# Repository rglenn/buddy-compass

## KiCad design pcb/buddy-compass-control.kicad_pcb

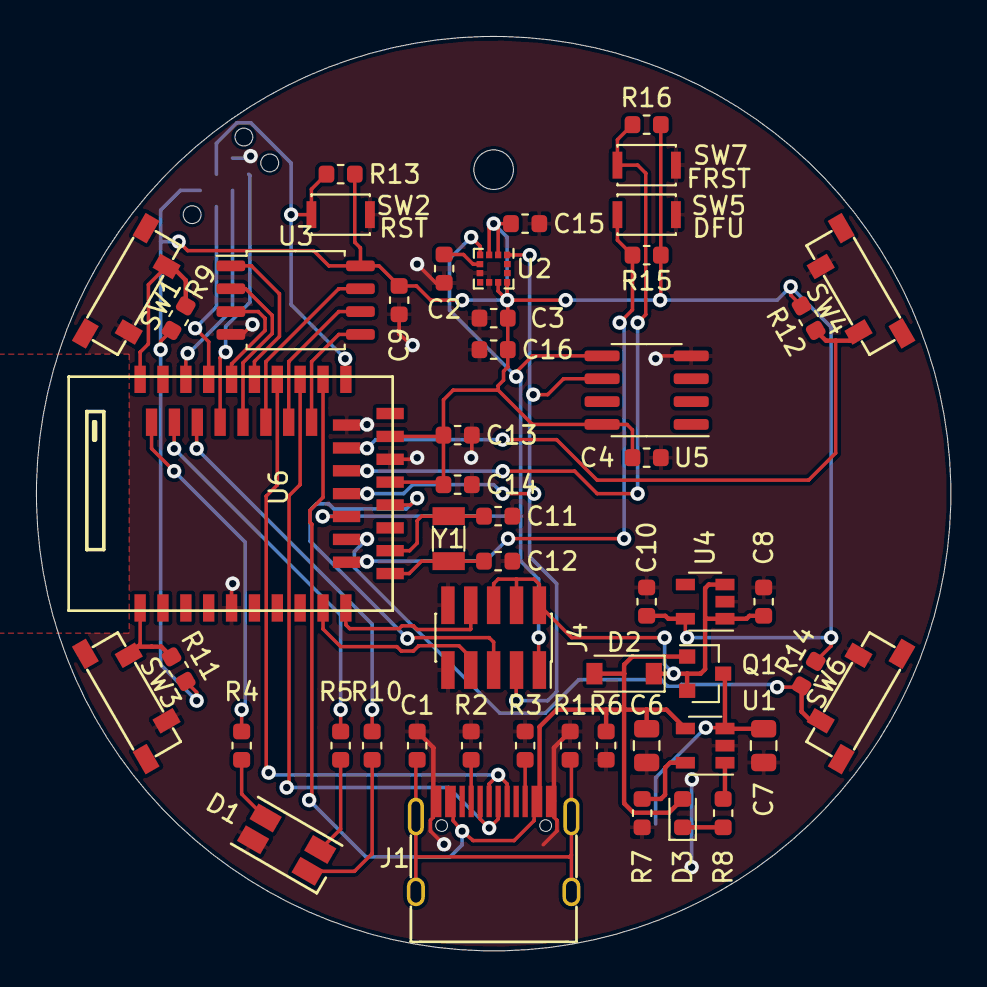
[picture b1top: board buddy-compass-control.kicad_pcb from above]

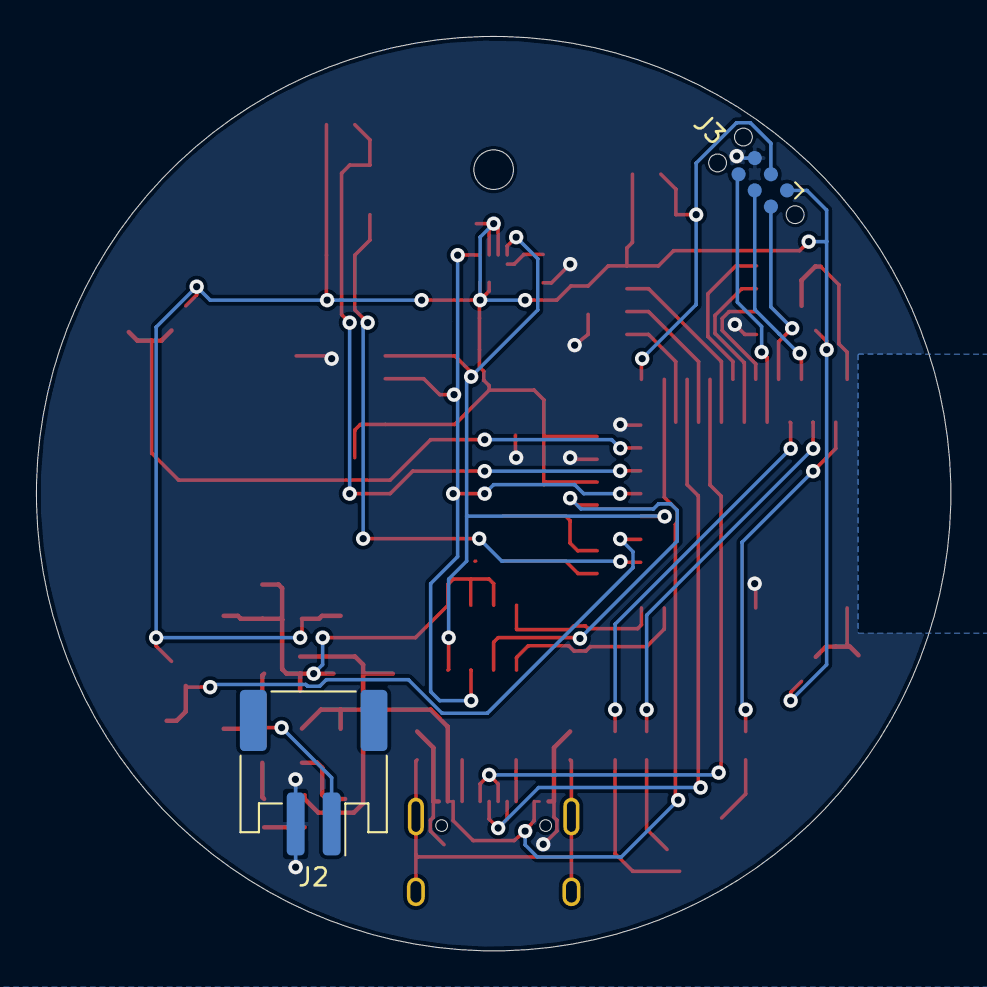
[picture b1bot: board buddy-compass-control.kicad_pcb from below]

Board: 2 copper layers, 50.8 x 50.8 mm, 54 parts (2 on the bottom side), 43 nets.

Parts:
C1, C3, C4, C9, C14, C15: 100n; C_0603_1608Metric
C2: 220n; C_0603_1608Metric
C6, C7: 4.7u; C_0805_2012Metric
C8, C10, C13, C16: 1u; C_0603_1608Metric
C11, C12: 12p; C_0603_1608Metric
D1: LED_RGBC; LED_RGB_1210
D2: MBR0520; D_SOD-123
D3: LED; LED_0603_1608Metric
H1: MountingHole; MountingHole_2.2mm_M2_DIN965
J1: USB_C_Receptacle_USB2.0; USB_C_Receptacle_GT-USB-7010
J2: Conn_01x02; JST_PH_S2B-PH-SM4-TB_1x02-1MP_P2.00mm_Horizontal
J3: Conn_02x03_Odd_Even; Tag-Connect_TC2030-IDC-NL_2x03_P1.27mm_Vertical
J4: Conn_02x05_Odd_Even; PinSocket_2x05_P1.27mm_Vertical_SMD
Q1: DMG2301L; SOT-23
R1: 1M; R_0603_1608Metric
R2, R3: 5.1K; R_0603_1608Metric
R4, R5, R10: 220; R_0603_1608Metric
R6: 100K; R_0603_1608Metric
R7: 2K; R_0603_1608Metric
R8: 1K; R_0603_1608Metric
R9, R11, R12, R13, R14, R15, R16: 47K; R_0603_1608Metric
SW1, SW3, SW4, SW6: SW_Push; TS-1236VW
SW2, SW5, SW7: SW_Push; SW_SPST_CK_KXT3
U1: MCP73831-2-OT; SOT-23-5
U2: LSM303C; LGA-12_2x2mm_Pitch0.5mm
U3: W25Q32JVSS; SOIC-8_5.23x5.23mm_P1.27mm
U4: MIC5504-3.3YM5; SOT-23-5
U5: ATECC608A-SSHDA; SOIC-8_3.9x4.9mm_P1.27mm
U6: E73-2G4M08S1C
Y1: 32.768KHz; Crystal_SMD_3215-2Pin_3.2x1.5mm

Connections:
+3V3: C3.1, C4.1, C9.1, C10.1, C13.1, C14.1, C15.1, C16.1, J3.1, R9.1, R11.1, R12.1, R13.1, R14.1, R15.1, R16.1, U2.2, U2.3, U2.9, U2.10, U3.8, U4.5, U5.8, U6.19, U6.23
/BUTTON1: R9.2, SW1.1, U6.43
/BUTTON3: R11.2, SW3.1, U6.1
/BUTTON4: R12.2, SW4.1, U6.22
/BUTTON6: R14.2, SW6.1, U6.14
/D+: J1.A6, J1.B6, U6.31
/D-: J1.A7, J1.B7, U6.29
/DFU: R15.2, SW5.1, U6.12
/DISPLAY_IO1: J4.7, U6.9
/DISPLAY_IO2: J4.8, U6.10
/FRST: R16.2, SW7.1, U6.20
/QSPI_CS: U3.1, U6.33
/QSPI_D0: U3.5, U6.28
/QSPI_D1: U3.2, U6.34
/QSPI_D2: U3.3, U6.35
/QSPI_D3: U3.7, U6.32
/QSPI_SCK: U3.6, U6.30
/RESET: J3.3, R13.2, SW2.1, U6.26
/SCL: J4.3, U2.1, U5.6, U6.18
/SDA: J4.1, U2.4, U5.5, U6.16
/SDB: J4.5, U6.17
/STATUS_B: R4.1, U6.42
/STATUS_G: R5.1, U6.40
/STATUS_R: R10.1, U6.38
/SWC: J3.4, U6.39
/SWD: J3.2, U6.37
/SWO: J3.6, U6.36
GND: C1.2, C2.2, C3.2, C4.2, C6.2, C7.2, C8.2, C9.2, C10.2, C11.2, C12.2, C13.2, C14.2, C15.2, C16.2, D1.4, J1.A1, J1.A12, J1.B1, J1.B12, J2.2, J3.5, J4.9, J4.10, R1.2, R2.2, R3.2, R6.2, R7.2, SW1.2, SW2.2, SW3.2, SW4.2, SW5.2, SW6.2, SW7.2, U1.2, U2.6, U2.8, U3.4, U4.2, U5.4, U6.5, U6.21, U6.24
unnamed: C1.1, J1.S1, R1.1
unnamed: C2.1, U2.5
unnamed: C7.1, J2.1, Q1.3, U1.3
unnamed: C11.1, U6.13, Y1.2
unnamed: C12.1, U6.11, Y1.1
unnamed: D1.1, R10.2
unnamed: D1.2, R5.2
unnamed: D1.3, R4.2
unnamed: D3.1, R8.1
unnamed: J1.A5, R2.1
unnamed: J1.B5, R3.1
unnamed: R7.1, U1.5
unnamed: R8.2, U1.1
VBUS: C6.1, D2.2, D3.2, J1.A4, J1.A9, J1.B4, J1.B9, Q1.1, R6.1, U1.4, U6.27
VCC: C8.1, D2.1, J4.2, J4.4, J4.6, Q1.2, U4.1, U4.3

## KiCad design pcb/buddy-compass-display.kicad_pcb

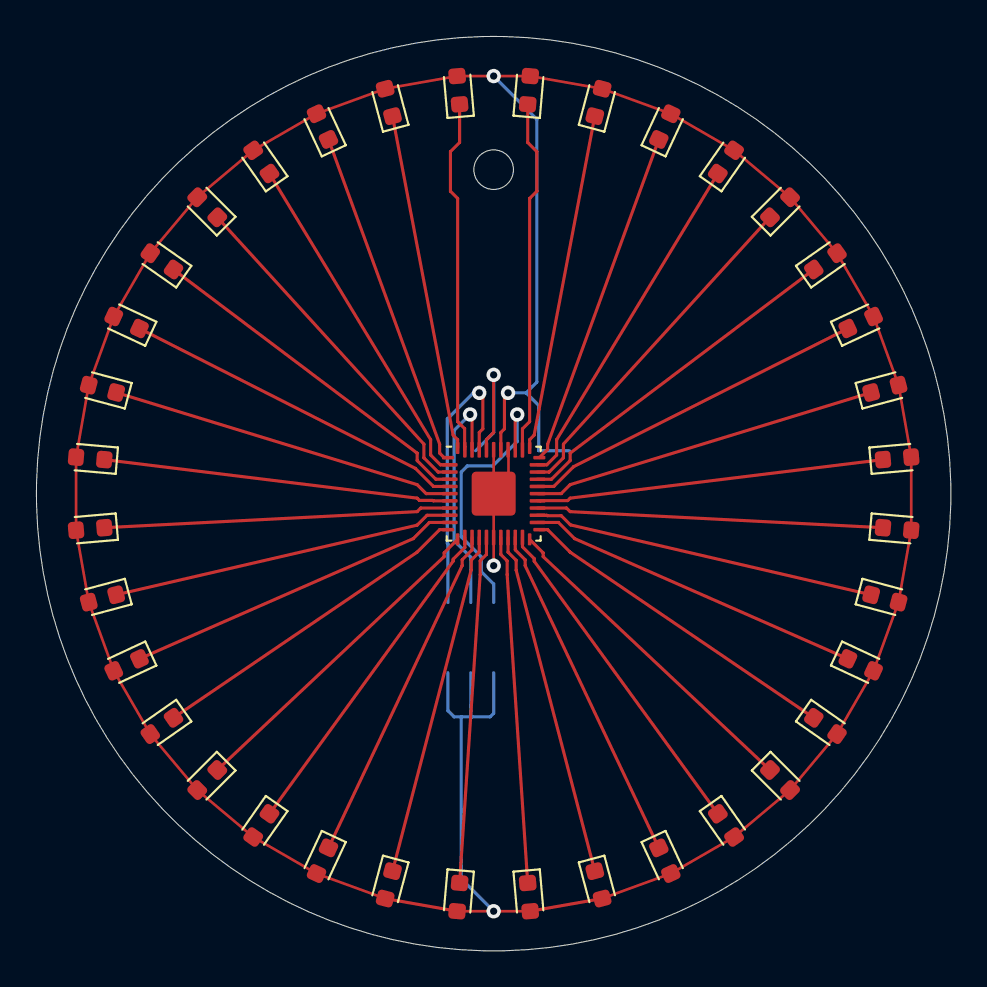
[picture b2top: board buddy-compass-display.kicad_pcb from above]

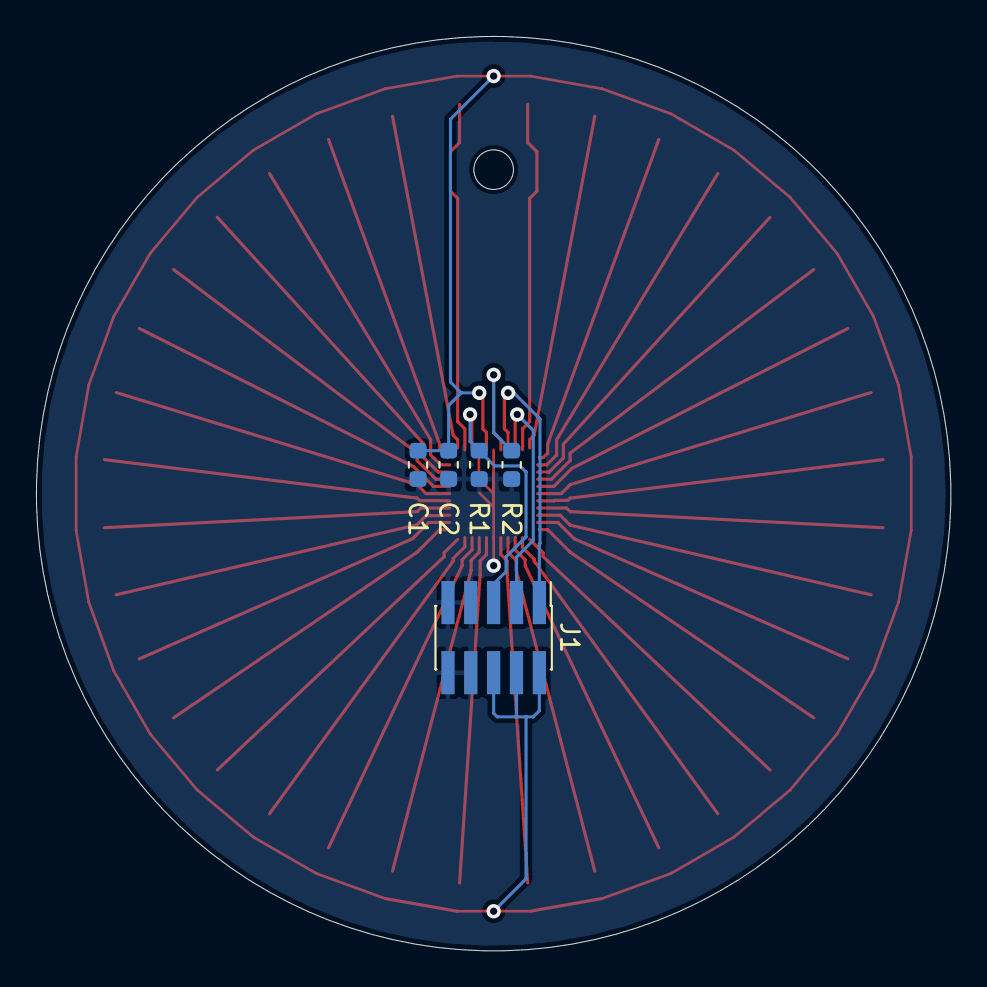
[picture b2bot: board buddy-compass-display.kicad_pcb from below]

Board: 2 copper layers, 50.8 x 50.8 mm, 43 parts (5 on the bottom side), 42 nets.

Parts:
C1: 1u; C_0603_1608Metric
C2: 100n; C_0603_1608Metric
D1, D2, D3, D4, D5, D6, D7, D8, D9, D10, D11, D12, D13, D14, D15, D16, D17, D18, D19, D20, D21, D22, D23, D24, D25, D26, D27, D28, D29, D30, D31, D32, D33, D34, D35, D36: LED; LED_0603_1608Metric
H1: MountingHole; MountingHole_2.2mm_M2_DIN965
J1: Conn_02x05_Odd_Even; PinHeader_2x05_P1.27mm_Vertical_SMD
R1: 100K; R_0603_1608Metric
R2: 3.3K; R_0603_1608Metric
U1: IS31FL3236A; QFN-44-1EP_5x5mm_P0.4mm_EP2.45x2.45mm

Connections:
/SCL: J1.3, U1.42
/SDA: J1.1, U1.41
/SDB: J1.5, R1.1, U1.36
GND: C1.2, C2.2, J1.7, J1.8, J1.9, J1.10, R1.2, R2.2, U1.17, U1.37, U1.39, U1.45
unnamed: D1.1, U1.35
unnamed: D2.1, U1.34
unnamed: D3.1, U1.33
unnamed: D4.1, U1.32
unnamed: D5.1, U1.31
unnamed: D6.1, U1.30
unnamed: D7.1, U1.29
unnamed: D8.1, U1.28
unnamed: D9.1, U1.27
unnamed: D10.1, U1.26
unnamed: D11.1, U1.25
unnamed: D12.1, U1.24
unnamed: D13.1, U1.23
unnamed: D14.1, U1.22
unnamed: D15.1, U1.21
unnamed: D16.1, U1.20
unnamed: D17.1, U1.19
unnamed: D18.1, U1.18
unnamed: D19.1, U1.16
unnamed: D20.1, U1.15
unnamed: D21.1, U1.14
unnamed: D22.1, U1.13
unnamed: D23.1, U1.12
unnamed: D24.1, U1.11
unnamed: D25.1, U1.10
unnamed: D26.1, U1.9
unnamed: D27.1, U1.8
unnamed: D28.1, U1.7
unnamed: D29.1, U1.6
unnamed: D30.1, U1.5
unnamed: D31.1, U1.4
unnamed: D32.1, U1.3
unnamed: D33.1, U1.2
unnamed: D34.1, U1.1
unnamed: D35.1, U1.44
unnamed: D36.1, U1.43
unnamed: R2.1, U1.40
VCC: C1.1, C2.1, D1.2, D2.2, D3.2, D4.2, D5.2, D6.2, D7.2, D8.2, D9.2, D10.2, D11.2, D12.2, D13.2, D14.2, D15.2, D16.2, D17.2, D18.2, D19.2, D20.2, D21.2, D22.2, D23.2, D24.2, D25.2, D26.2, D27.2, D28.2, D29.2, D30.2, D31.2, D32.2, D33.2, D34.2, D35.2, D36.2, J1.2, J1.4, J1.6, U1.38

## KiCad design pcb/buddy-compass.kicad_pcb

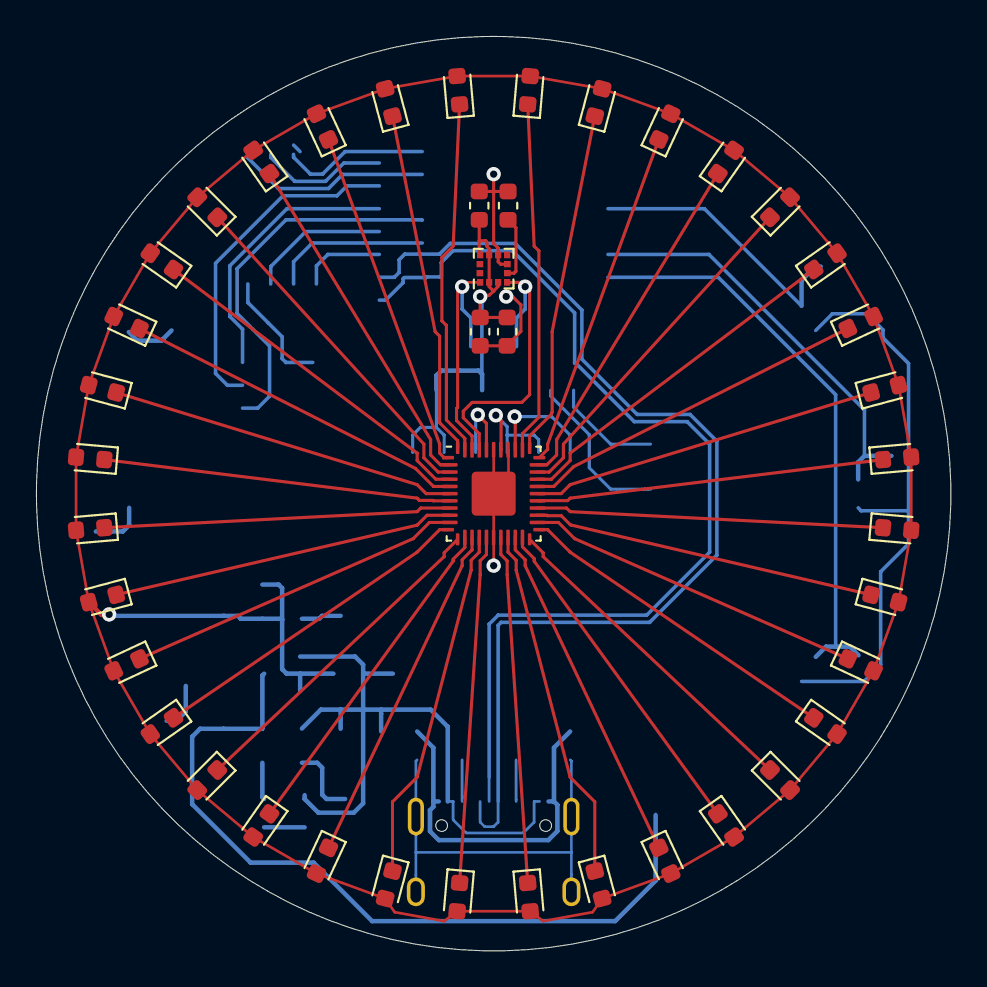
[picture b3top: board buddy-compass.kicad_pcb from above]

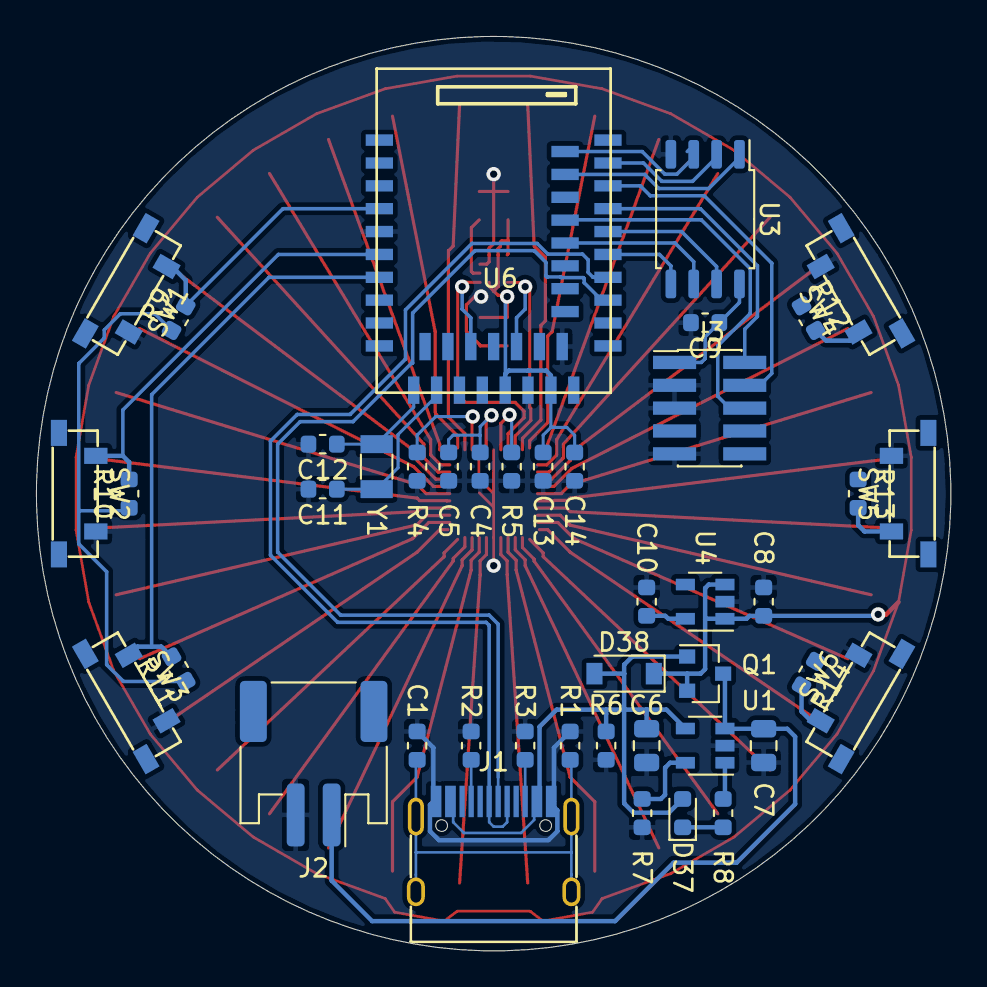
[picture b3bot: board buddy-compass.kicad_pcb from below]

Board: 2 copper layers, 50.8 x 50.8 mm, 85 parts (43 on the bottom side), 72 nets.

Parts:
C1, C3, C5, C9, C14, C15: 100n; C_0603_1608Metric
C2: 220n; C_0603_1608Metric
C4, C8, C10, C13, C16: 1u; C_0603_1608Metric
C6, C7: 4.7u; C_0805_2012Metric
C11, C12: 12p; C_0603_1608Metric
D1, D2, D3, D4, D5, D6, D7, D8, D9, D10, D11, D12, D13, D14, D15, D16, D17, D18, D19, D20, D21, D22, D23, D24, D25, D26, D27, D28, D29, D30, D31, D32, D33, D34, D35, D36, D37: LED; LED_0603_1608Metric
D38: MBR0520; D_SOD-123
J1: USB_C_Receptacle_USB2.0; USB_C_Receptacle_GT-USB-7010
J2: Conn_01x02; JST_PH_S2B-PH-SM4-TB_1x02-1MP_P2.00mm_Horizontal
J3: Conn_ARM_JTAG_SWD_10; PinHeader_2x05_P1.27mm_Vertical_SMD
Q1: DMG2301L; SOT-23
R1: 1M; R_0603_1608Metric
R2, R3: 5.1K; R_0603_1608Metric
R4, R6: 100K; R_0603_1608Metric
R5: 3.3K; R_0603_1608Metric
R7: 2K; R_0603_1608Metric
R8: 1K; R_0603_1608Metric
R9, R10, R11, R12, R13, R14: 47K; R_0603_1608Metric
SW1, SW2, SW3, SW4, SW5, SW6: SW_Push; TS-1236VW
U1: MCP73831-2-OT; SOT-23-5
U2: LSM303C; LGA-12_2x2mm_Pitch0.5mm
U3: W25Q32JVSS; SOIC-8_5.23x5.23mm_P1.27mm
U4: MIC5504-3.3YM5; SOT-23-5
U5: IS31FL3236A; QFN-44-1EP_5x5mm_P0.4mm_EP2.45x2.45mm
U6: E73-2G4M08S1C
Y1: 32.768KHz; Crystal_SMD_3215-2Pin_3.2x1.5mm

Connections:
+3V3: C3.1, C9.1, C10.1, C13.1, C14.1, C15.1, C16.1, J3.1, R9.1, R10.1, R11.1, R12.1, R13.1, R14.1, U2.2, U2.3, U2.9, U2.10, U3.8, U4.5, U6.19, U6.23
/BUTTON1: R9.2, SW1.1, U6.4
/BUTTON2: R10.2, SW2.1, U6.6
/BUTTON3: R11.2, SW3.1, U6.7
/BUTTON4: R12.2, SW4.1, U6.43
/BUTTON5: R13.2, SW5.1, U6.28
/BUTTON6: R14.2, SW6.1, U6.22
/D+: J1.A6, J1.B6, U6.31
/D-: J1.A7, J1.B7, U6.29
/QSPI_CS: U3.1, U6.40
/QSPI_D0: U3.5, U6.33
/QSPI_D1: U3.2, U6.41
/QSPI_D2: U3.3, U6.42
/QSPI_D3: U3.7, U6.35
/QSPI_SCK: U3.6, U6.34
/RESET: J3.10, U6.26
/SCL: U2.1, U5.42, U6.20
/SDA: U2.4, U5.41, U6.16
/SWC: J3.4, U6.39
/SWD: J3.2, U6.37
/SWO: J3.6, U6.36
GND: C1.2, C2.2, C3.2, C4.2, C5.2, C6.2, C7.2, C8.2, C9.2, C10.2, C11.2, C12.2, C13.2, C14.2, C15.2, C16.2, J1.A1, J1.A12, J1.B1, J1.B12, J2.2, J3.3, J3.5, J3.9, R1.2, R2.2, R3.2, R4.2, R5.2, R6.2, R7.2, SW1.2, SW2.2, SW3.2, SW4.2, SW5.2, SW6.2, U1.2, U2.6, U2.8, U3.4, U4.2, U5.17, U5.37, U5.39, U5.45, U6.5, U6.21, U6.24
unnamed: C1.1, J1.S1, R1.1
unnamed: C2.1, U2.5
unnamed: C7.1, J2.1, Q1.3, U1.3
unnamed: C11.1, U6.13, Y1.2
unnamed: C12.1, U6.11, Y1.1
unnamed: D1.1, U5.35
unnamed: D2.1, U5.34
unnamed: D3.1, U5.33
unnamed: D4.1, U5.32
unnamed: D5.1, U5.31
unnamed: D6.1, U5.30
unnamed: D7.1, U5.29
unnamed: D8.1, U5.28
unnamed: D9.1, U5.27
unnamed: D10.1, U5.26
unnamed: D11.1, U5.25
unnamed: D12.1, U5.24
unnamed: D13.1, U5.23
unnamed: D14.1, U5.22
unnamed: D15.1, U5.21
unnamed: D16.1, U5.20
unnamed: D17.1, U5.19
unnamed: D18.1, U5.18
unnamed: D19.1, U5.16
unnamed: D20.1, U5.15
unnamed: D21.1, U5.14
unnamed: D22.1, U5.13
unnamed: D23.1, U5.12
unnamed: D24.1, U5.11
unnamed: D25.1, U5.10
unnamed: D26.1, U5.9
unnamed: D27.1, U5.8
unnamed: D28.1, U5.7
unnamed: D29.1, U5.6
unnamed: D30.1, U5.5
unnamed: D31.1, U5.4
unnamed: D32.1, U5.3
unnamed: D33.1, U5.2
unnamed: D34.1, U5.1
unnamed: D35.1, U5.44
unnamed: D36.1, U5.43
unnamed: D37.1, R8.1
unnamed: J1.A5, R2.1
unnamed: J1.B5, R3.1
unnamed: R4.1, U5.36
unnamed: R5.1, U5.40
unnamed: R7.1, U1.5
unnamed: R8.2, U1.1
VBUS: C6.1, D37.2, D38.2, J1.A4, J1.A9, J1.B4, J1.B9, Q1.1, R6.1, U1.4, U6.27
VCC: C4.1, C5.1, C8.1, D1.2, D2.2, D3.2, D4.2, D5.2, D6.2, D7.2, D8.2, D9.2, D10.2, D11.2, D12.2, D13.2, D14.2, D15.2, D16.2, D17.2, D18.2, D19.2, D20.2, D21.2, D22.2, D23.2, D24.2, D25.2, D26.2, D27.2, D28.2, D29.2, D30.2, D31.2, D32.2, D33.2, D34.2, D35.2, D36.2, D38.1, Q1.2, U4.1, U4.3, U5.38

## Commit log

2019-12-29 Adding first efforts on schematic and PCB. Still need footprint for BLE module.
2020-01-09 Updating schematic and PCB with LEDs laid out in a circle
2020-01-10 Making some progress on the top layout. Need to rework around the compass.
2020-01-20 Added buttons and footprint for MCU module. Layout for buttons and power supply is done. Still need to tweak sensor layout and LED driver layout to fit MCU underneath.
2020-01-28 I think I've routed myself into a corner - no way to lay this out properly on 2-layer without adding extraneous stuff to top layer, which would spoil the look.
    Moving to a 2-board solution.
2020-01-28 Added display-only board
2020-01-28 Adding control-only board. Needs work.
2020-02-09 Control board routing finished.
2020-02-09 Committing unsaved schematic changes
2020-02-15 Added Atmel crypto chip. Renumbered some diodes. Added extra pins on display connector to allow display blanking and future upgrades.
